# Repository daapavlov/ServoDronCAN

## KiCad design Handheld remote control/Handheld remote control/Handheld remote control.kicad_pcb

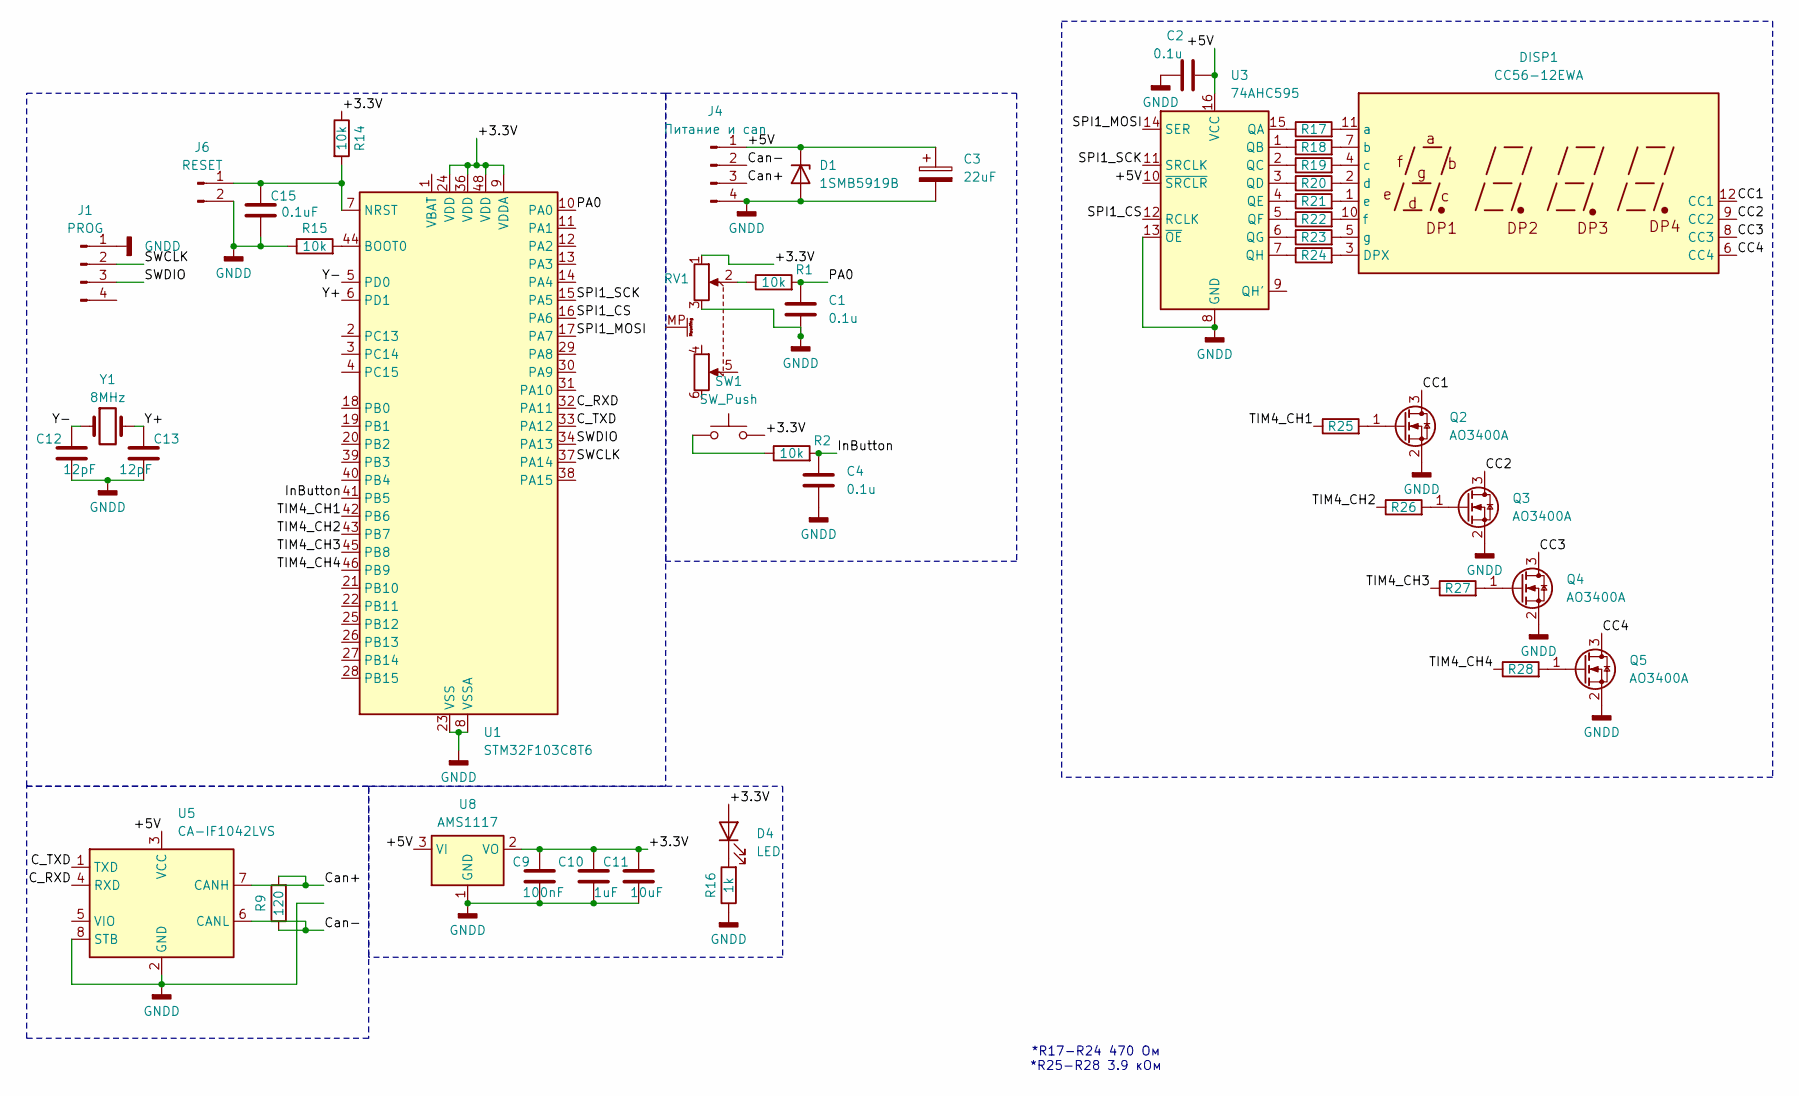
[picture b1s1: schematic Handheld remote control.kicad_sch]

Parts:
C1, C2, C4: 0.1u; C_0805_2012Metric_Pad1.18x1.45mm_HandSolder
C3: 22uF; CP_Radial_D10.0mm_P2.50mm
C9: 100nF; C_0805_2012Metric
C10: 1uF; C_0805_2012Metric
C11: 10uF; C_0805_2012Metric
C12, C13: 12pF; C_0805_2012Metric
C15: 0.1uF; C_0805_2012Metric
D1: 1SMB5919B; D_SMB
D4: LED; LED_0805_2012Metric
DISP1: CC56-12EWA; CA56-12EWA
J1: PROG; JST_XH_B4B-XH-A_1x04_P2.50mm_Vertical
J4: Питание и can; PhoenixContact_MC_1,5_4-G-3.5_1x04_P3.50mm_Horizontal
J6: RESET; PinHeader_1x02_P2.54mm_Vertical
Q2, Q3, Q4, Q5: AO3400A; SOT-23
R1, R2, R14, R15: 10k; R_0805_2012Metric
R9: 120; R_0805_2012Metric
R16: 1k; R_0805_2012Metric
R17, R18, R19, R20, R21, R22, R23, R24: 470; R_0805_2012Metric
R25, R26, R27, R28: 3.3k; R_0805_2012Metric
RV1: R_Potentiometer_Dual_MountingPin; Potentiometer_Bourns_PTV112-4_Dual_Vertical
SW1: SW_Push; SW_SPST_Omron_B3FS-100xP
U1: STM32F103C8T6; LQFP-48_7x7mm_P0.5mm; Operating Voltage Range 2V~3.6V; Low Voltage Detection T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 2V~3.6V; Part STM32F103C8T6; LCSC C8734
U3: 74AHC595; SOIC-16_3.9x9.9mm_P1.27mm
U5: CA-IF1042LVS; SOIC-8_3.9x4.9mm_P1.27mm
U8: AMS1117; SOT-223-3_TabPin2
Y1: 8MHz; Crystal_HC49-U_Vertical

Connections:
/+3.3V: C9.1, C10.1, C11.1, D4.2 (A), R14.1, RV1.1, SW1.2, U1.9 (VDDA), U1.24 (VDD), U1.36 (VDD), U1.48 (VDD), U8.2 (VO)
/+5V: C2.2, C3.1, D1.1 (K), J4.1, U3.10 (~SRCLR), U3.16 (VCC), U5.3 (VCC), U8.3 (VI)
/C_RXD: U1.32 (PA11), U5.4 (RXD)
/C_TXD: U1.33 (PA12), U5.1 (TXD)
/Can+: J4.3, R9.2, U5.7 (CANH)
/Can-: J4.2, R9.1, U5.6 (CANL)
/InButton: C4.1, R2.2, U1.41 (PB5)
/PA0: C1.1, R1.2, U1.10 (PA0)
/SPI1_CS: U1.16 (PA6), U3.12 (RCLK)
/SPI1_MOSI: U1.17 (PA7), U3.14 (SER)
/SPI1_SCK: U1.15 (PA5), U3.11 (SRCLK)
/SWCLK: J1.2, U1.37 (PA14)
/SWDIO: J1.3, U1.34 (PA13)
/TIM4_CH1: R25.1, U1.42 (PB6)
/TIM4_CH2: R26.1, U1.43 (PB7)
/TIM4_CH3: R27.1, U1.45 (PB8)
/TIM4_CH4: R28.1, U1.46 (PB9)
/Y+: C13.1, U1.6 (PD1), Y1.2
/Y-: C12.1, U1.5 (PD0), Y1.1
/СС1: DISP1.12 (CC1), Q2.3 (D)
/СС2: DISP1.9 (CC2), Q3.3 (D)
/СС3: DISP1.8 (CC3), Q4.3 (D)
/СС4: DISP1.6 (CC4), Q5.3 (D)
GNDD: C1.2, C2.1, C3.2, C4.2, C9.2, C10.2, C11.2, C12.2, C13.2, C15.2, D1.2 (A), J1.1, J4.4, J6.2, Q2.2 (S), Q3.2 (S), Q4.2 (S), Q5.2 (S), R15.1, R16.1, RV1.3, U1.8 (VSSA), U1.23 (VSS), U1.35 (VSS), U1.47 (VSS), U3.8 (GND), U3.13 (~OE), U5.2 (GND), U5.8 (STB), U8.1 (GND)
unnamed: D4.1 (K), R16.2
unnamed: DISP1.3 (DPX), R24.2
unnamed: DISP1.11 (a), R17.2
unnamed: DISP1.7 (b), R18.2
unnamed: DISP1.4 (c), R19.2
unnamed: DISP1.2 (d), R20.2
unnamed: DISP1.1 (e), R21.2
unnamed: DISP1.10 (f), R22.2
unnamed: DISP1.5 (g), R23.2
unnamed: C15.1, J6.1, R14.2, U1.7 (NRST)
unnamed: Q2.1 (G), R25.2
unnamed: Q3.1 (G), R26.2
unnamed: Q4.1 (G), R27.2
unnamed: Q5.1 (G), R28.2
unnamed: R1.1, RV1.2
unnamed: R2.1, SW1.1
unnamed: R15.2, U1.44 (BOOT0)
unnamed: R17.1, U3.15 (QA)
unnamed: R18.1, U3.1 (QB)
unnamed: R19.1, U3.2 (QC)
unnamed: R20.1, U3.3 (QD)
unnamed: R21.1, U3.4 (QE)
unnamed: R22.1, U3.5 (QF)
unnamed: R23.1, U3.6 (QG)
unnamed: R24.1, U3.7 (QH)

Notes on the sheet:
*R17-R24 470 Ом *R25-R28 3.9 кОм

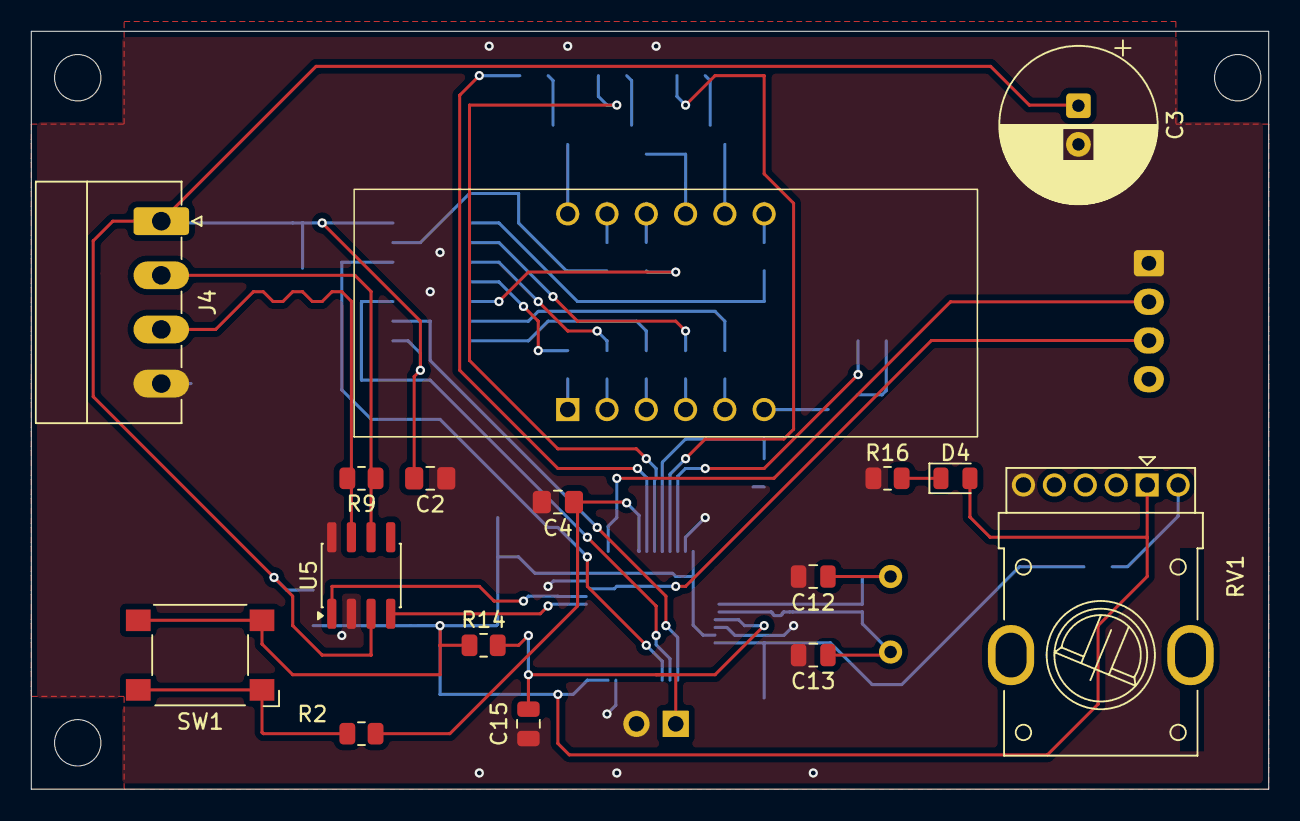
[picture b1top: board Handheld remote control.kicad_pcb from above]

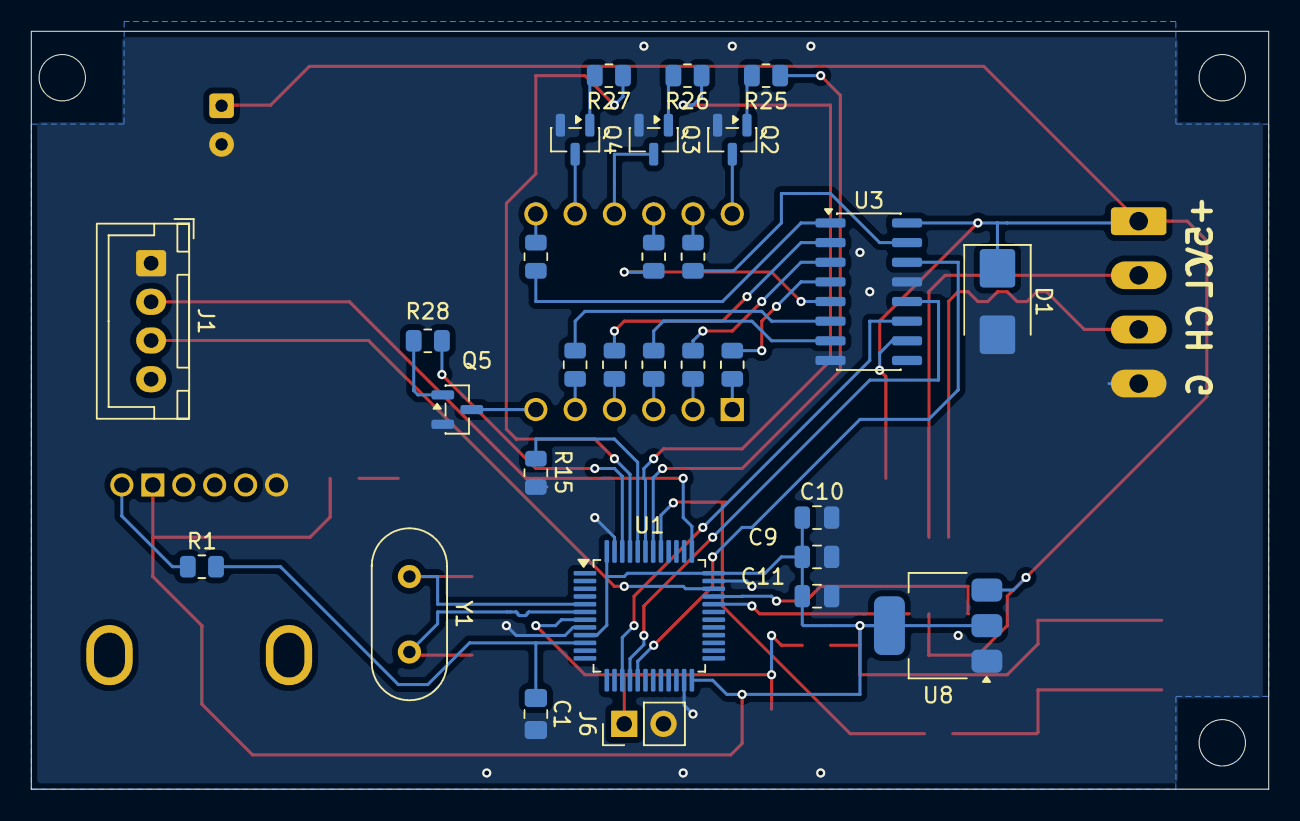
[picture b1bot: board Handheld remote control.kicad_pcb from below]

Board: 2 copper layers, 80.0 x 49.0 mm, 45 parts (29 on the bottom side), 49 nets.

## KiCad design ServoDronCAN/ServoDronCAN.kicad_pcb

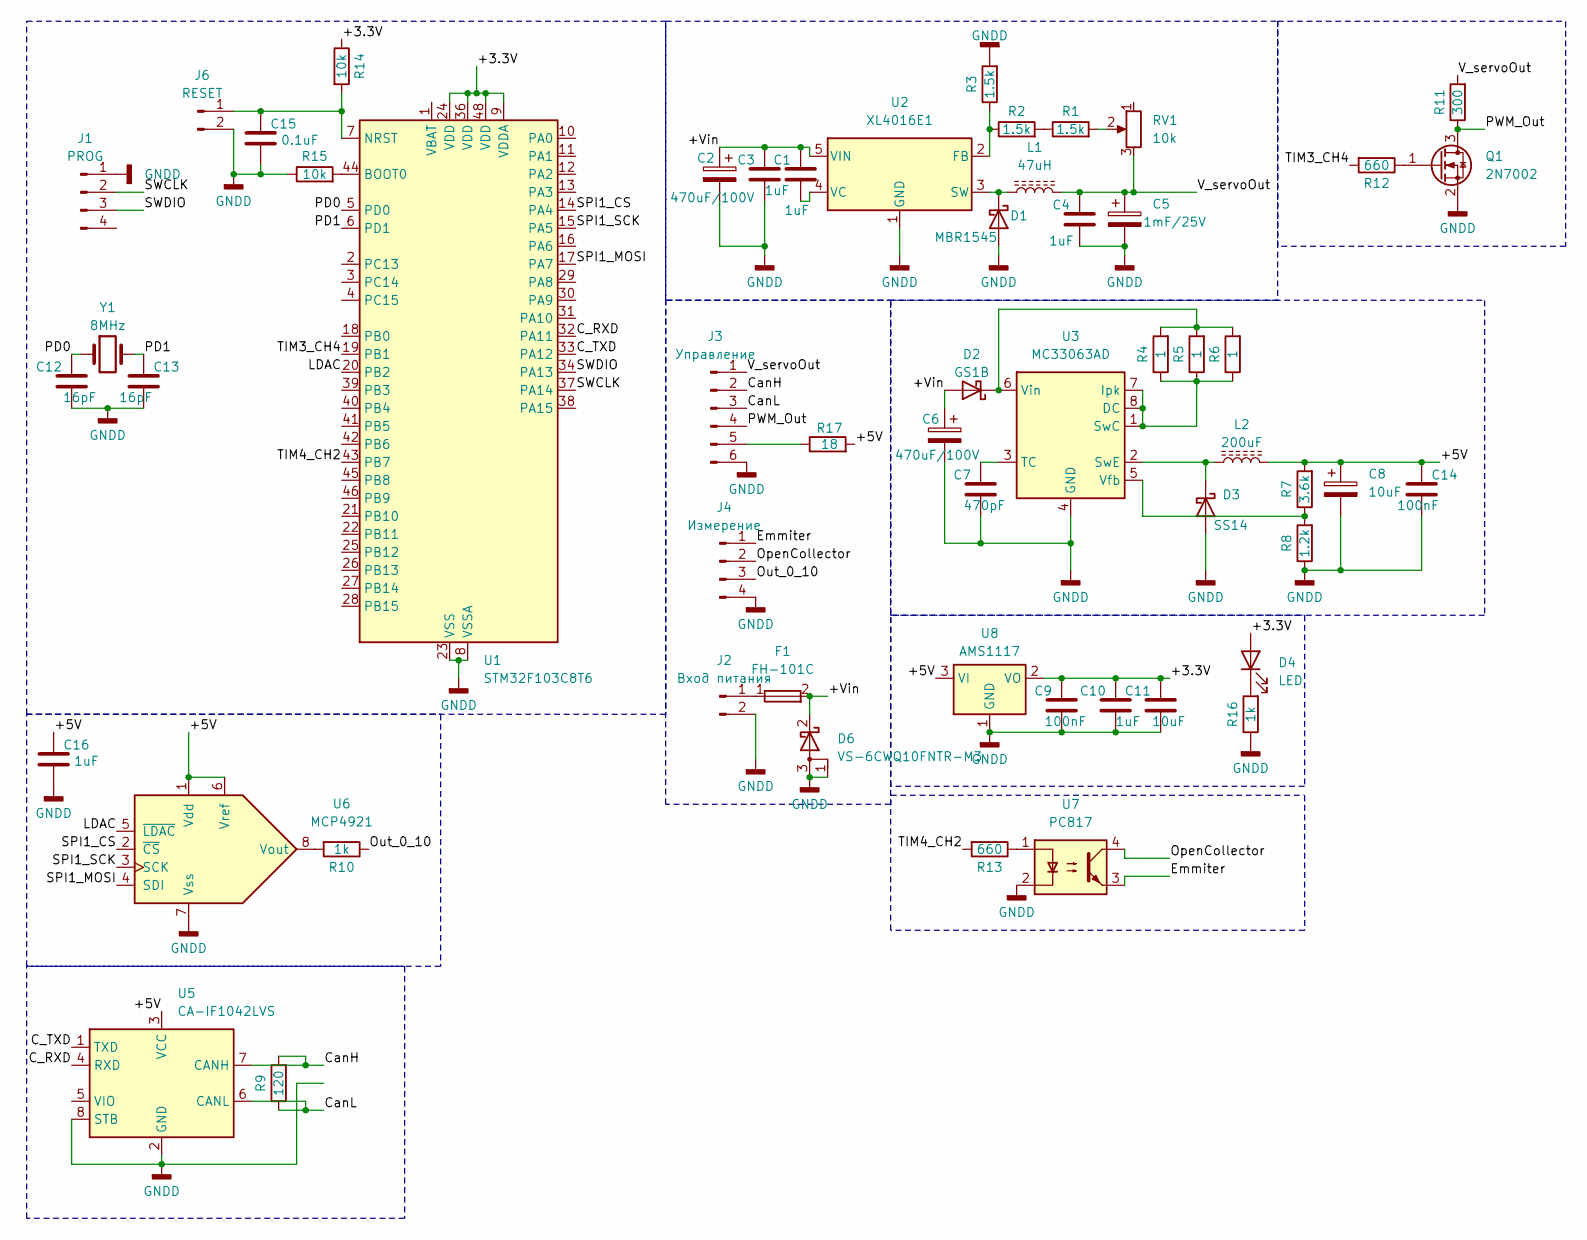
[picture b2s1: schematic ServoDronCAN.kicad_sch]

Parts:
C1, C3, C4, C10, C16: 1uF; C_0805_2012Metric
C2, C6: 470uF/100V; CP_Radial_D16.0mm_P7.50mm
C5: 1mF/25V; CP_Radial_D10.0mm_P5.00mm
C7: 470pF; C_0805_2012Metric
C8: 10uF; CP_Elec_4x5.4
C9, C14: 100nF; C_0805_2012Metric
C11: 10uF; C_0805_2012Metric
C12, C13: 16pF; C_0805_2012Metric
C15: 0.1uF; C_0805_2012Metric
D1: MBR1545; TO-220-2_Horizontal_TabUp
D2: GS1B; D_SMA
D3: SS14; D_SMA
D4: LED; LED_0805_2012Metric
D6: VS-6CWQ10FNTR-M3; TO-252-2
F1: FH-101C
J1: PROG; JST_XH_B4B-XH-A_1x04_P2.50mm_Vertical
J2: Вход питания; PhoenixContact_MC_1,5_2-G-3.5_1x02_P3.50mm_Horizontal
J3: Управление; PhoenixContact_MC_1,5_6-G-3.5_1x06_P3.50mm_Horizontal
J4: Измерение; PhoenixContact_MC_1,5_4-G-3.5_1x04_P3.50mm_Horizontal
J6: RESET; PinHeader_1x02_P2.54mm_Vertical
L1: 47uH; L_Toroid_Vertical_L31.8mm_W15.9mm_P13.50mm_Bourns_5700
L2: 200uF; L_10.4x10.4_H4.8
Q1: 2N7002; SOT-23-3
R1, R2, R3: 1.5k; R_0805_2012Metric
R4, R5, R6: 1; R_0805_2012Metric
R7: 3.6k; R_0805_2012Metric
R8: 1.2k; R_0805_2012Metric
R9: 120; R_0805_2012Metric
R10, R16: 1k; R_0805_2012Metric
R11: 300; R_0805_2012Metric
R12, R13: 660; R_0805_2012Metric
R14, R15: 10k; R_0805_2012Metric
R17: 18; R_Axial_DIN0516_L15.5mm_D5.0mm_P20.32mm_Horizontal
RV1: 10k; Potentiometer_Bourns_3296W_Vertical
U1: STM32F103C8T6; LQFP-48_7x7mm_P0.5mm; Operating Voltage Range 2V~3.6V; Low Voltage Detection T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 2V~3.6V; Part STM32F103C8T6; LCSC C8734
U2: XL4016E1; TO-220-5_P3.4x3.8mm_StaggerOdd_Lead7.13mm_TabDown
U3: MC33063AD; SOIC-8_3.9x4.9mm_P1.27mm
U5: CA-IF1042LVS; SOIC-8_3.9x4.9mm_P1.27mm
U6: MCP4921; SOIC-8_3.9x4.9mm_P1.27mm
U7: PC817; DIP-4_W7.62mm
U8: AMS1117; SOT-223-3_TabPin2
Y1: 8MHz; Crystal_HC49-U_Vertical

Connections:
/+3.3V: C9.1, C10.1, C11.1, D4.2 (A), R14.1, U1.9 (VDDA), U1.24 (VDD), U1.36 (VDD), U1.48 (VDD), U8.2 (VO)
/+5V: C8.1, C14.1, C16.1, J3.5, L2.2, R7.2, R17.1, R17.2, U5.3 (VCC), U6.1 (Vdd), U6.6 (Vref), U8.3 (VI)
/+Vin: C1.1, C2.1, C3.1, C6.1, D2.2 (A), D6.2 (K), F1.2, U2.5 (VIN)
/C_RXD: U1.32 (PA11), U5.4 (RXD)
/C_TXD: U1.33 (PA12), U5.1 (TXD)
/CanH: J3.2, R9.2, U5.7 (CANH)
/CanL: J3.3, R9.1, U5.6 (CANL)
/Emmiter: J4.1, U7.3
/LDAC: U1.20 (PB2), U6.5 (~LDAC)
/OpenCollector: J4.2, U7.4
/Out_0_10: J4.3, R10.1
/PD0: C12.1, U1.5 (PD0), Y1.1
/PD1: C13.1, U1.6 (PD1), Y1.2
/PWM_Out: J3.4, Q1.3 (D), R11.1
/SPI1_CS: U1.14 (PA4), U6.2 (~CS)
/SPI1_MOSI: U1.17 (PA7), U6.4 (SDI)
/SPI1_SCK: U1.15 (PA5), U6.3 (SCK)
/SWCLK: J1.2, U1.37 (PA14)
/SWDIO: J1.3, U1.34 (PA13)
/TIM3_CH4: R12.2, U1.19 (PB1)
/TIM4_CH2: R13.2, U1.43 (PB7)
/V_servoOut: C4.1, C5.1, J3.1, L1.2, R11.2, RV1.3
GNDD: C2.2, C3.2, C4.2, C5.2, C6.2, C7.2, C8.2, C9.2, C10.2, C11.2, C12.2, C13.2, C14.2, C15.2, C16.2, D1.2 (A), D3.2 (A), D6.1 (A), D6.3 (A), J1.1, J2.2, J3.6, J4.4, J6.2, Q1.2 (S), R3.2, R8.1, R15.1, R16.1, U1.8 (VSSA), U1.23 (VSS), U1.35 (VSS), U1.47 (VSS), U2.1 (GND), U3.4 (GND), U5.2 (GND), U5.8 (STB), U6.7 (Vss), U7.2, U8.1 (GND)
unnamed: D1.1 (K), L1.1, U2.3 (SW)
unnamed: D2.1 (K), R4.2, R5.2, R6.2, U3.6 (Vin)
unnamed: D3.1 (K), L2.1, U3.2 (SwE)
unnamed: D4.1 (K), R16.2
unnamed: F1.1, J2.1
unnamed: C15.1, J6.1, R14.2, U1.7 (NRST)
unnamed: Q1.1 (G), R12.1
unnamed: R1.1, R2.2
unnamed: R1.2, RV1.2
unnamed: R13.1, U7.1
unnamed: R15.2, U1.44 (BOOT0)
unnamed: R2.1, R3.1, U2.2 (FB)
unnamed: C1.2, U2.4 (VC)
unnamed: R4.1, R5.1, R6.1, U3.1 (SwC), U3.7 (Ipk), U3.8 (DC)
unnamed: C7.1, U3.3 (TC)
unnamed: R7.1, R8.2, U3.5 (Vfb)
unnamed: R10.2, U6.8 (Vout)

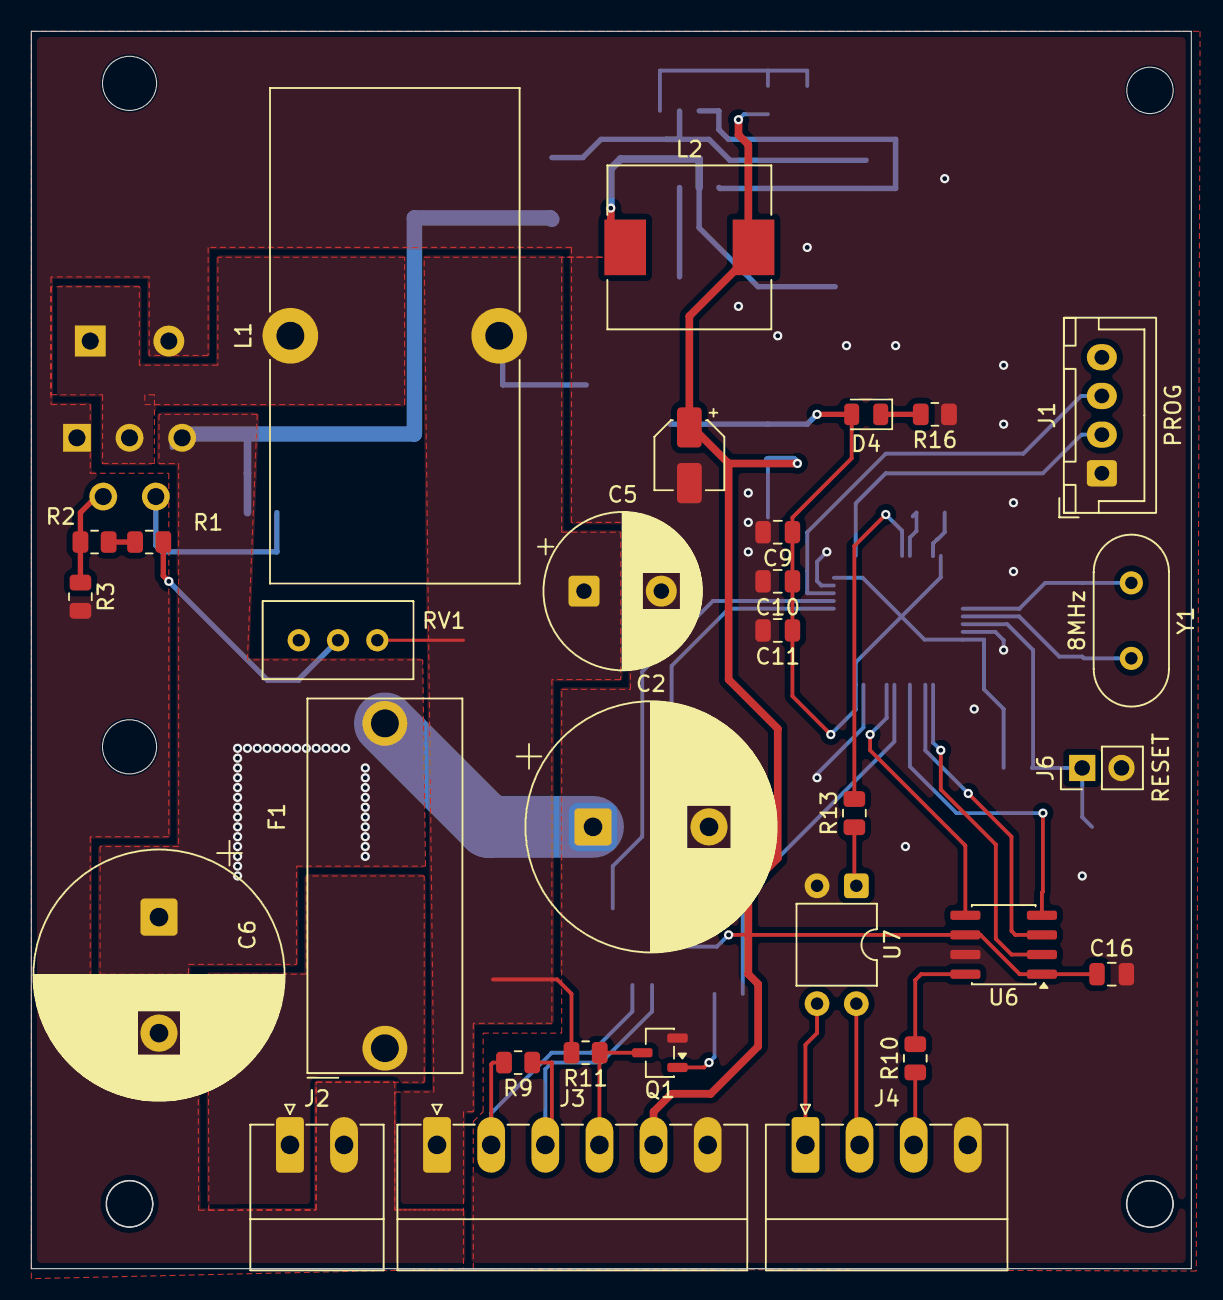
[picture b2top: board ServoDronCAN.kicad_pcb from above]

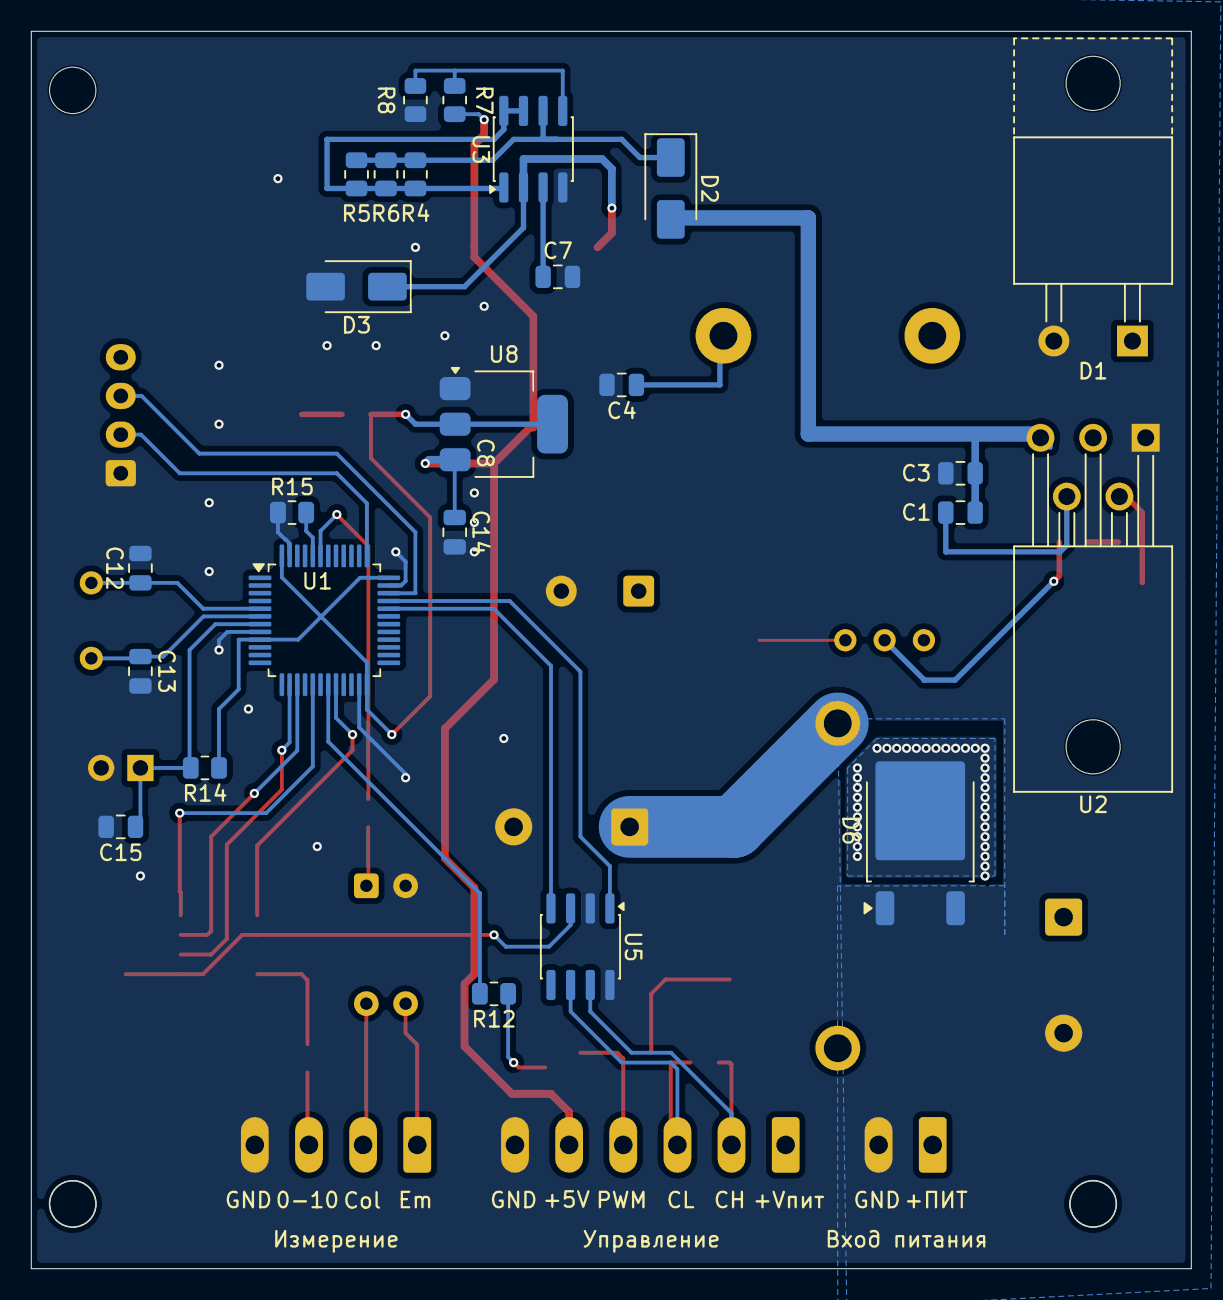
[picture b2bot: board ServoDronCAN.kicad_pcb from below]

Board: 2 copper layers, 75.0 x 80.0 mm, 55 parts (25 on the bottom side), 40 nets.

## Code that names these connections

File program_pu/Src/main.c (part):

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{
  __HAL_RCC_GPIOB_CLK_ENABLE();

  //PA0 - analog input
  GPIOA->CRL &= ~(GPIO_CRL_MODE0_Msk | GPIO_CRL_CNF0_Msk);
  //PA5 - SPI SCLK Alternate function push-pull
  GPIOA->CRL &= ~(GPIO_CRL_MODE5_Msk | GPIO_CRL_CNF5_Msk);
  GPIOA->CRL |= (0b11<<GPIO_CRL_MODE5_Pos) | (0b10<<GPIO_CRL_CNF5_Pos);
  //PA6 - output push-pull
  GPIOA->CRL &= ~(GPIO_CRL_MODE6_Msk | GPIO_CRL_CNF6_Msk);
  GPIOA->CRL |= (0b11<<GPIO_CRL_MODE6_Pos);
  GPIOA->CRL |= (0b00<<GPIO_CRL_CNF6_Pos);
  //PA7 - SPI MOSI Alternate function push-pull
  GPIOA->CRL &= ~(GPIO_CRL_MODE7_Msk | GPIO_CRL_CNF7_Msk);
  GPIOA->CRL |= (0b11<<GPIO_CRL_MODE7_Pos) | (0b10<<GPIO_CRL_CNF7_Pos);
  //PB0 - output push-pull
  GPIOB->CRL &= ~(GPIO_CRL_MODE0_Msk | GPIO_CRL_CNF0_Msk);
  GPIOB->CRL |= (0b11<<GPIO_CRL_MODE0_Pos);
  GPIOB->CRL |= (0b00<<GPIO_CRL_CNF0_Pos);
  //PB1 - output CH
  GPIOB->CRL &= ~(GPIO_CRL_MODE1_Msk | GPIO_CRL_CNF1_Msk);
  GPIOB->CRL |= (0b10<<GPIO_CRL_CNF1_Pos | 0b11<<GPIO_CRL_MODE1_Pos);
  //PB12-PB15 - output push-pull
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  GPIOB->CRH |= (0b11<<GPIO_CRH_MODE12_Pos | 0b00<<GPIO_CRH_CNF12_Pos | 0b11<<GPIO_CRH_MODE13_Pos | 0b00<<GPIO_CRH_CNF13_Pos |
      0b11<<GPIO_CRH_MODE14_Pos | 0b00<<GPIO_CRH_CNF14_Pos | 0b11<<GPIO_CRH_MODE15_Pos | 0b00<<GPIO_CRH_CNF15_Pos);
  GPIOB->CRH |= (0b00<<GPIO_CRL_CNF0_Pos); //PB0 Output push-pull
  //PB4-PB7 - reserved
  //PB6 & PB7 - output push-pull
  GPIOB->CRL &= ~(GPIO_CRL_MODE6_Msk | GPIO_CRL_CNF6_Msk);
  GPIOB->CRL |= (0b11<<GPIO_CRL_MODE6_Pos);
  GPIOB->CRL |= (0b00<<GPIO_CRL_CNF6_Pos);
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  GPIOB->CRL |= (0b00<<GPIO_CRL_CNF7_Pos);
  GPIOB->BSRR |= GPIO_BSRR_BR7;
  
  //PB8 & PB9 - output push-pull
  GPIOB->CRH &= ~(GPIO_CRH_MODE8_Msk | GPIO_CRH_CNF8_Msk);
  GPIOB->CRH |= (0b11<<GPIO_CRH_MODE8_Pos);
  GPIOB->CRH |= (0b00<<GPIO_CRH_CNF8_Pos);
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  GPIOB->CRH |= (0b11<<GPIO_CRH_MODE9_Pos);
  GPIOB->CRH |= (0b00<<GPIO_CRH_CNF9_Pos);
  GPIOB->BSRR |= GPIO_BSRR_BR9;
  //PB5 - input 
  GPIOB->CRL &= ~(GPIO_CRL_MODE5_Msk | GPIO_CRL_CNF5_Msk);
  GPIOB->CRL |= (0b10<<GPIO_CRL_CNF5_Pos | 0b00<<GPIO_CRL_MODE5_Pos);
  /*AFIO->EXTICR[1] |= AFIO_EXTICR2_EXTI6_PB;
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
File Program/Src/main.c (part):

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{
  __HAL_RCC_GPIOB_CLK_ENABLE();

  //PA0 - analog input
  GPIOA->CRL &= ~(GPIO_CRL_MODE0_Msk | GPIO_CRL_CNF0_Msk);
  //PA5 - SPI SCLK Alternate function push-pull
  GPIOA->CRL &= ~(GPIO_CRL_MODE5_Msk | GPIO_CRL_CNF5_Msk);
  GPIOA->CRL |= (0b11<<GPIO_CRL_MODE5_Pos) | (0b10<<GPIO_CRL_CNF5_Pos);
  //PA4 - output push-pull
  GPIOA->CRL &= ~(GPIO_CRL_MODE4_Msk | GPIO_CRL_CNF4_Msk);
  GPIOA->CRL |= (0b11<<GPIO_CRL_MODE4_Pos);
  GPIOA->CRL |= (0b00<<GPIO_CRL_CNF4_Pos);
  GPIOA->BSRR |= GPIO_BSRR_BS4;
  //PA7 - SPI MOSI Alternate function push-pull
  GPIOA->CRL &= ~(GPIO_CRL_MODE7_Msk | GPIO_CRL_CNF7_Msk);
  GPIOA->CRL |= (0b11<<GPIO_CRL_MODE7_Pos) | (0b10<<GPIO_CRL_CNF7_Pos);
  //PB0 - output push-pull
  GPIOB->CRL &= ~(GPIO_CRL_MODE0_Msk | GPIO_CRL_CNF0_Msk);
  GPIOB->CRL |= (0b11<<GPIO_CRL_MODE0_Pos);
  GPIOB->CRL |= (0b00<<GPIO_CRL_CNF0_Pos);
  //PB1 - output CH
  GPIOB->CRL &= ~(GPIO_CRL_MODE1_Msk | GPIO_CRL_CNF1_Msk);
  GPIOB->CRL |= (0b10<<GPIO_CRL_CNF1_Pos | 0b11<<GPIO_CRL_MODE1_Pos);
  //PB2 - output push-pull
  GPIOB->CRL &= ~(GPIO_CRL_MODE2_Msk | GPIO_CRL_CNF2_Msk);
  GPIOB->CRL |= (0b11<<GPIO_CRL_MODE2_Pos);
  GPIOB->CRL |= (0b00<<GPIO_CRL_CNF2_Pos);
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  GPIOB->CRH |= (0b11<<GPIO_CRH_MODE12_Pos | 0b00<<GPIO_CRH_CNF12_Pos | 0b11<<GPIO_CRH_MODE13_Pos | 0b00<<GPIO_CRH_CNF13_Pos |
      0b11<<GPIO_CRH_MODE14_Pos | 0b00<<GPIO_CRH_CNF14_Pos | 0b11<<GPIO_CRH_MODE15_Pos | 0b00<<GPIO_CRH_CNF15_Pos);
  GPIOB->CRH |= (0b00<<GPIO_CRL_CNF0_Pos); //PB0 Output push-pull
  //PB4-PB7 - reserved
  //PB7 - output CH
  GPIOB->CRL &= ~(GPIO_CRL_MODE7_Msk | GPIO_CRL_CNF7_Msk);
  GPIOB->CRL |= (0b10<<GPIO_CRL_CNF7_Pos | 0b11<<GPIO_CRL_MODE7_Pos);

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  GPIOB->CRL |= (0b00<<GPIO_CRL_MODE4_Pos);
  GPIOB->CRL |= (0b10<<GPIO_CRL_CNF4_Pos);
  GPIOB->ODR &= ~GPIO_ODR_ODR4;
  //PB6 - input EXTI
  GPIOB->CRL &= ~(GPIO_CRL_MODE6_Msk | GPIO_CRL_CNF6_Msk);
  GPIOB->CRL |= (0b10<<GPIO_CRL_CNF6_Pos | 0b00<<GPIO_CRL_MODE6_Pos);
  /*AFIO->EXTICR[1] |= AFIO_EXTICR2_EXTI6_PB;
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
